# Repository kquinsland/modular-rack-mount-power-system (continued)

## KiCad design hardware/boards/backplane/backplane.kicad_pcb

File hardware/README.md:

# Hardware

Source hardware lives here.

- `boards/`: One KiCad project per physical PCB.
- `libraries/`: Project-local KiCad symbols, footprints, and 3D models shared by all boards.
- `mechanical/`: Enclosure, panel, mounting, and exported mechanical references.

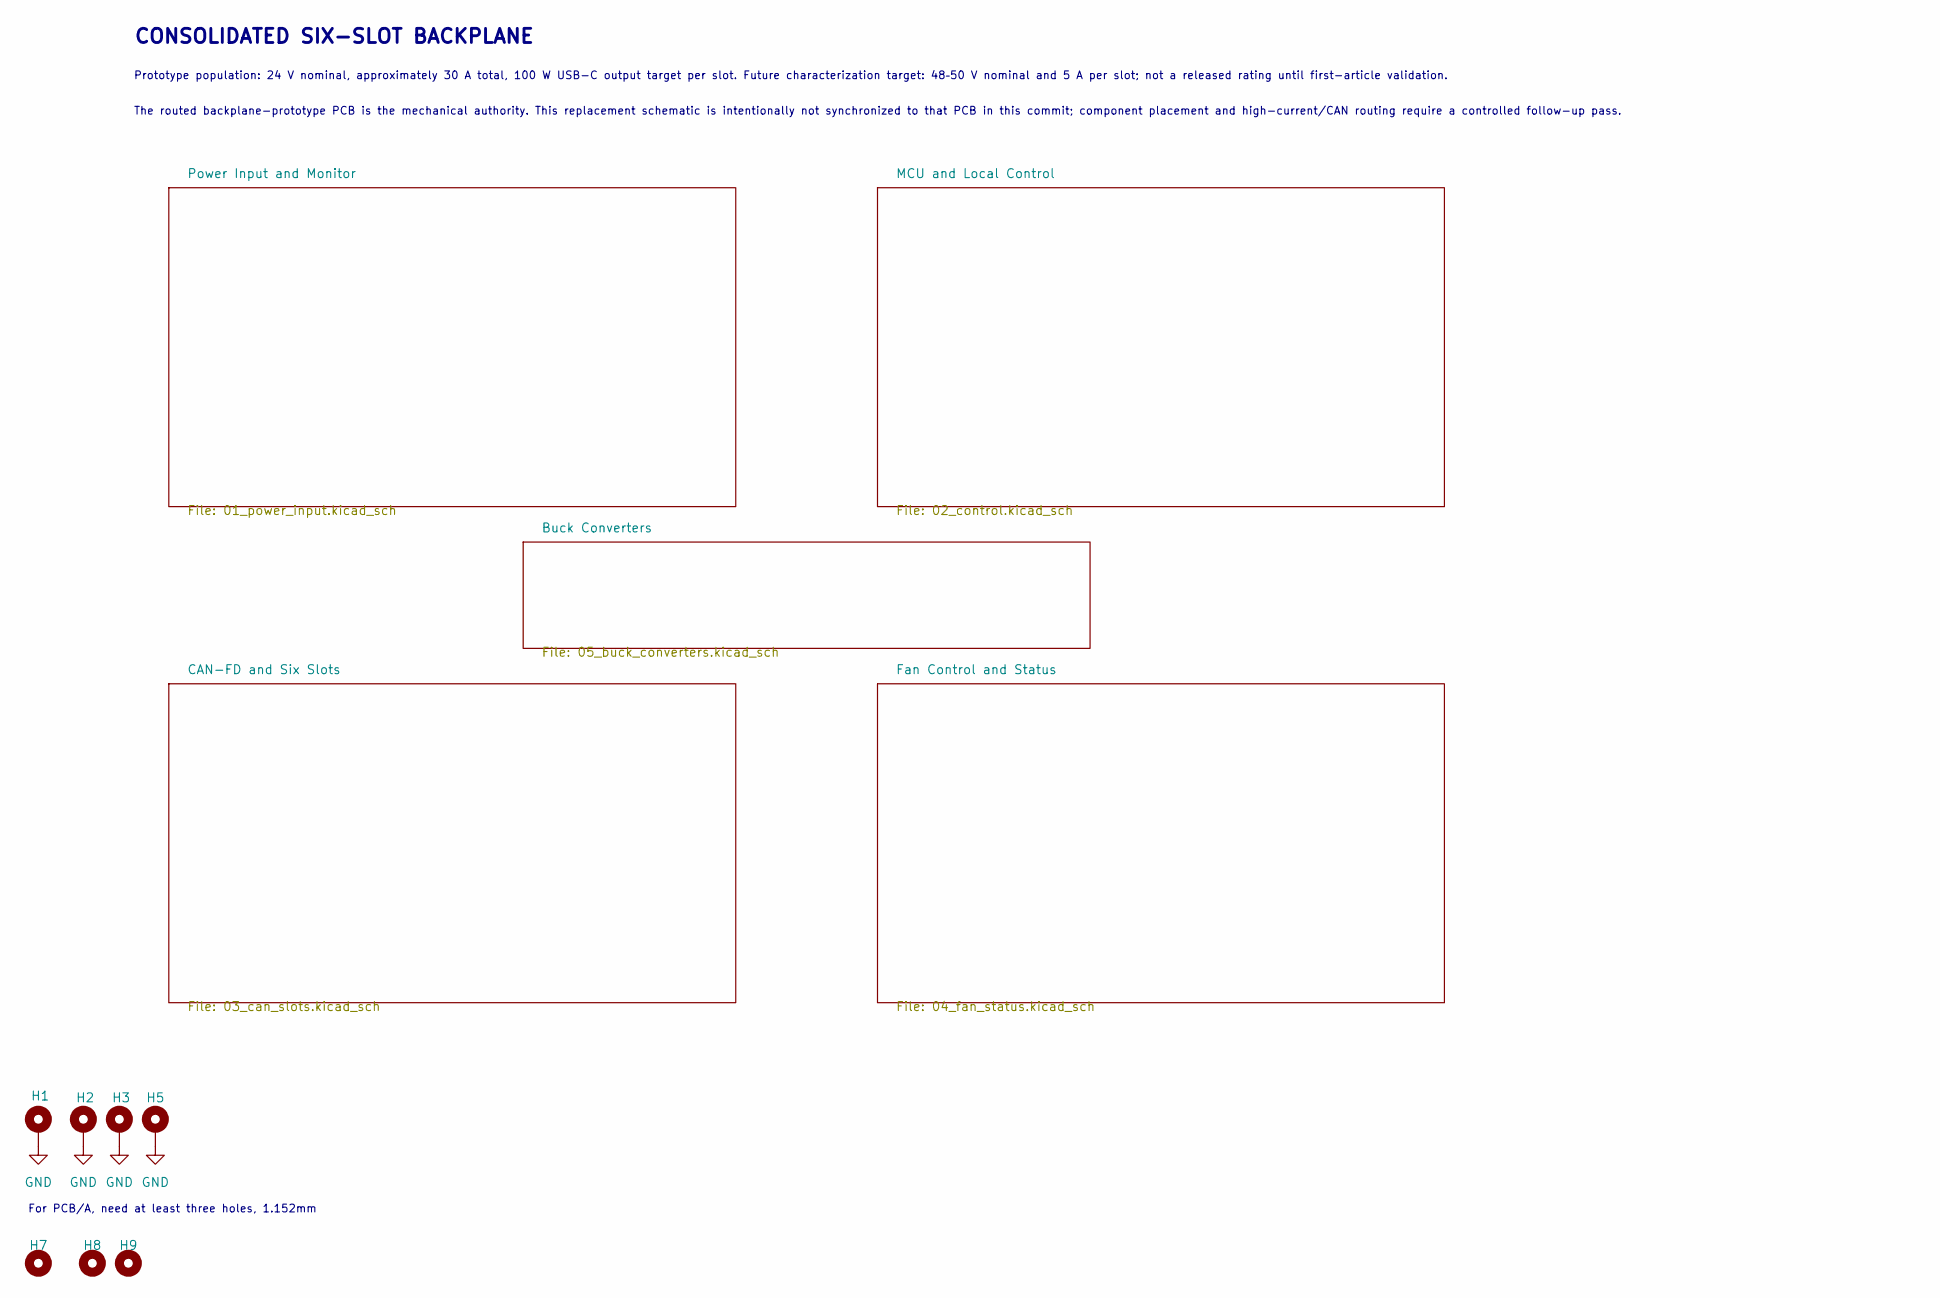
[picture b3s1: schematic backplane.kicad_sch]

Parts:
H1, H2, H3, H5: M2 CHASSIS; MountingHole_2.2mm_M2_Pad_Via_JLC
H7, H8, H9: ToolingHole_1.152mm; MountingHole_JLCPCB_Tooling_1.152mm

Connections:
GND: H1.1 (1_1), H2.1 (1_1), H3.1 (1_1), H5.1 (1_1); also elsewhere on the board

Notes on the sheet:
The routed backplane-prototype PCB is the mechanical authority. This replacement schematic is intentionally not synchronized to that PCB in this commit; component placement and high-current/CAN routing require a controlled follow-up pass.
Prototype population: 24 V nominal, approximately 30 A total, 100 W USB-C output target per slot. Future characterization target: 48–50 V nominal and 5 A per slot; not a released rating until first-article validation.
CONSOLIDATED SIX-SLOT BACKPLANE
For PCB/A, need at least three holes, 1.152mm

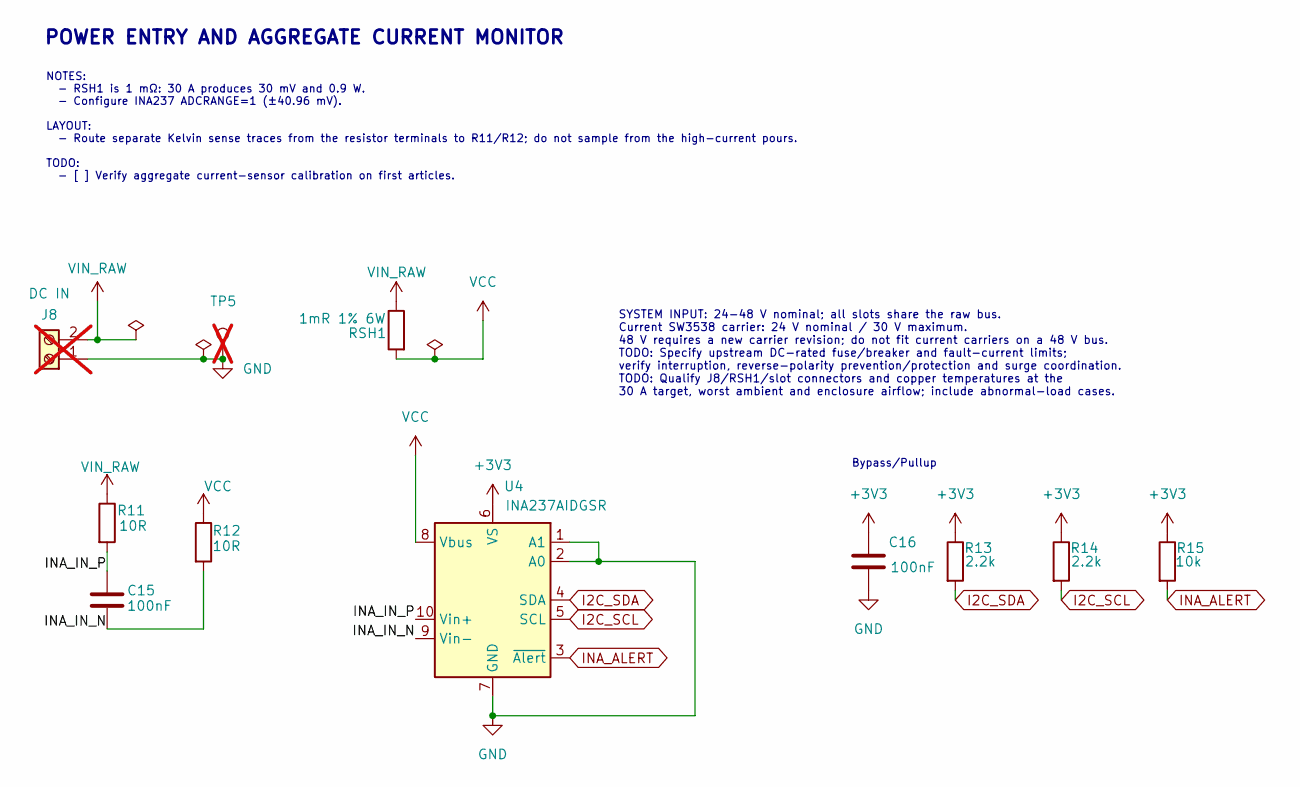
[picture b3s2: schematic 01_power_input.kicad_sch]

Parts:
C15, C16: 100nF; C_0603_1608Metric; Voltage 50 V; MPN CC0603KRX7R9BB104; LCSC C14663
J8: DC IN; DORABO_DB910-6.35-2P-GN-S; MPN DB910-6.35-2P-GN-S; LCSC C395872; not fitted
R11, R12: 10R; R_0603_1608Metric; Tolerance 1%; MPN 0603WAF100JT5E; LCSC C22859
R13, R14: 2.2k; R_0603_1608Metric; Tolerance 1%; MPN 0603WAF2201T5E; LCSC C4190
R15: 10k; R_0603_1608Metric; Tolerance 1%; MPN 0603WAF1002T5E; LCSC C25804
RSH1: 1mR 1% 6W; R_2512_6332Metric; Tolerance 1%; MPN HoLSX2512-6W-1mR-1%; LCSC C19270875
TP5: GND; TestPoint_Pad_D1.5mm; not fitted
U4: INA237AIDGSR; MSOP-10_3x3mm_P0.5mm_0.20mm_Clearance; MPN INA237AIDGSR; LCSC C2864837

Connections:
+3V3: C16.1, R13.1, R14.1, R15.1, U4.6 (VS); also elsewhere on the board
/Power Input and Monitor/INA_IN_N: C15.2, R12.2, U4.9 (Vin-)
/Power Input and Monitor/INA_IN_P: C15.1, R11.2, U4.10 (Vin+)
GND: C16.2, J8.1, TP5.1 (1_1), U4.1 (A1), U4.2 (A0), U4.7 (GND); also elsewhere on the board
I2C_SCL: R14.2, U4.5 (SCL); also elsewhere on the board
I2C_SDA: R13.2, U4.4 (SDA); also elsewhere on the board
INA_ALERT: R15.2, U4.3 (~Alert); also elsewhere on the board
VCC: R12.1, RSH1.2, U4.8 (Vbus); also elsewhere on the board
VIN_RAW: J8.2, R11.1, RSH1.1

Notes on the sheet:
NOTES: - RSH1 is 1 mΩ: 30 A produces 30 mV and 0.9 W. - Configure INA237 ADCRANGE=1 (±40.96 mV). LAYOUT: - Route separate Kelvin sense traces from the resistor terminals to R11/R12; do not sample from the high-current pours. TODO: - [ ] Verify aggregate current-sensor calibration on first articles.
Bypass/Pullup
SYSTEM INPUT: 24-48 V nominal; all slots share the raw bus. Current SW3538 carrier: 24 V nominal / 30 V maximum. 48 V requires a new carrier revision; do not fit current carriers on a 48 V bus. TODO: Specify upstream DC-rated fuse/breaker and fault-current limits; verify interruption, reverse-polar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
POWER ENTRY AND AGGREGATE CURRENT MONITOR

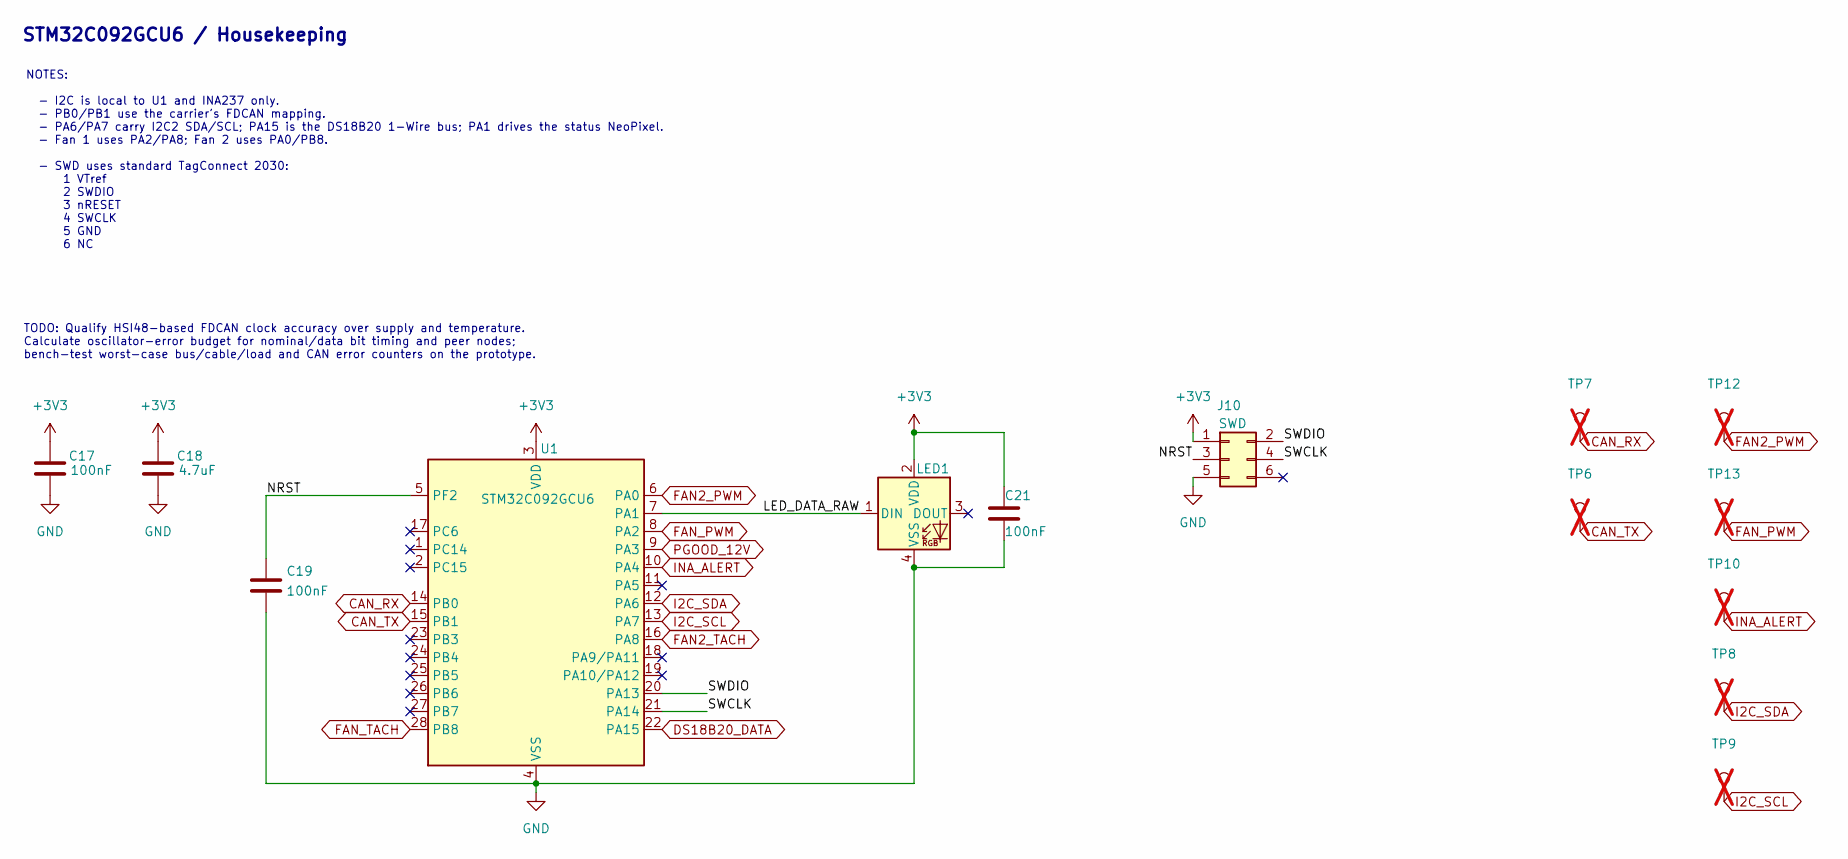
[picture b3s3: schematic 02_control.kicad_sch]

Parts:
C17, C19: 100nF; C_0603_1608Metric; Voltage 50 V; MPN CC0603KRX7R9BB104; LCSC C14663
C18: 4.7uF; C_0603_1608Metric; Voltage 10 V or greater; MPN CL10A475KO8NNNC; LCSC C19666
C21: 100nF; C_0603_1608Metric; MPN CC0603KRX7R9BB104; LCSC C14663
J10: SWD; Tag-Connect_TC2030-IDC-NL_2x03_P1.27mm_Vertical; MPN TC2030-IDC-NL
LED1: WS2812B-4020-V6; LED_Worldsemi_WS2812B-4020-V6_SideView; MPN WS2812B-4020-V6; LCSC C52941387
TP6: CAN_TX; TestPoint_Pad_D1.5mm; not fitted
TP7: CAN_RX; TestPoint_Pad_D1.5mm; not fitted
TP8: I2C_SDA; TestPoint_Pad_D1.5mm; not fitted
TP9: I2C_SCL; TestPoint_Pad_D1.5mm; not fitted
TP10: INA_ALERT; TestPoint_Pad_D1.5mm; not fitted
TP12, TP13: FAN_PWM; TestPoint_Pad_D1.5mm; not fitted
U1: STM32C092GCU6; QFN-28_4x4mm_P0.5mm; MPN STM32C092GCU6; LCSC C44847705

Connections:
+3V3: C17.1, C18.1, C21.1, J10.1, LED1.2 (VDD), U1.3 (VDD); also elsewhere on the board
/MCU and Local Control/LED_DATA_RAW: LED1.1 (DIN), U1.7 (PA1)
/MCU and Local Control/NRST: C19.1, J10.3, U1.5 (PF2)
/MCU and Local Control/SWCLK: J10.4, U1.21 (PA14)
/MCU and Local Control/SWDIO: J10.2, U1.20 (PA13)
CAN_RX: TP7.1 (1_1), U1.14 (PB0); also elsewhere on the board
CAN_TX: TP6.1 (1_1), U1.15 (PB1); also elsewhere on the board
DS18B20_DATA: U1.22 (PA15); also elsewhere on the board
FAN2_PWM: TP12.1 (1_1), U1.6 (PA0); also elsewhere on the board
FAN2_TACH: U1.16 (PA8); also elsewhere on the board
FAN_PWM: TP13.1 (1_1), U1.8 (PA2); also elsewhere on the board
FAN_TACH: U1.28 (PB8); also elsewhere on the board
GND: C17.2, C18.2, C19.2, C21.2, J10.5, LED1.4 (VSS), U1.4 (VSS); also elsewhere on the board
I2C_SCL: TP9.1 (1_1), U1.13 (PA7); also elsewhere on the board
I2C_SDA: TP8.1 (1_1), U1.12 (PA6); also elsewhere on the board
INA_ALERT: TP10.1 (1_1), U1.10 (PA4); also elsewhere on the board
PGOOD_12V: U1.9 (PA3); also elsewhere on the board

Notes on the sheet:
TODO: Qualify HSI48-based FDCAN clock accuracy over supply and temperature. Calculate oscillator-error budget for nominal/data bit timing and peer nodes; bench-test worst-case bus/cable/load and CAN error counters on the prototype.
STM32C092GCU6 / Housekeeping
NOTES: - I2C is local to U1 and INA237 only. - PB0/PB1 use the carrier's FDCAN mapping. - PA6/PA7 carry I2C2 SDA/SCL; PA15 is the DS18B20 1-Wire bus; PA1 drives the status NeoPixel. - Fan 1 uses PA2/PA8; Fan 2 uses PA0/PB8. - SWD uses standard TagConnect 2030: 1 VTref 2 SWDIO 3 nRESET 4 SWCLK 5 GND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

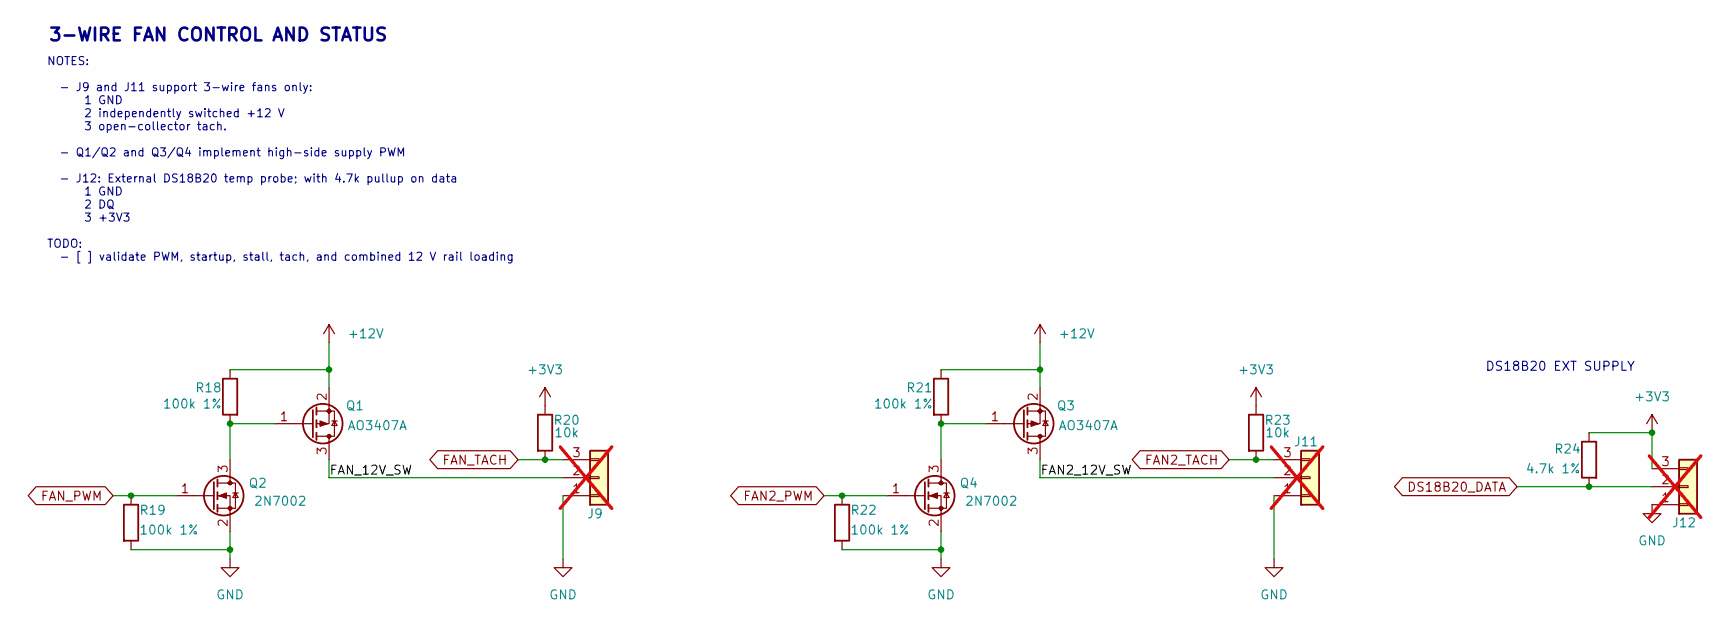
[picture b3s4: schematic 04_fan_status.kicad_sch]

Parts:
J9, J11: 12V 3-WIRE FAN; FanPinHeader_1x03_P2.54mm_Vertical_JLC_Edge; MPN TBD / user fan header; not fitted
J12: DS18B20 EXT SUPPLY; PinHeader_1x03_P2.54mm_Vertical; MPN TBD / user pin header; not fitted
Q1, Q3: AO3407A; SOT-23; MPN AO3407A; LCSC C15155
Q2, Q4: 2N7002; SOT-23; MPN 2N7002; LCSC C8545
R18, R19, R21, R22: 100k 1%; R_0603_1608Metric; Tolerance 1%; MPN 0603WAF1003T5E; LCSC C25803
R20, R23: 10k; R_0603_1608Metric; Tolerance 1%; MPN 0603WAF1002T5E; LCSC C25804
R24: 4.7k 1%; R_0603_1608Metric; Tolerance 1%; MPN 0603WAF4701T5E; LCSC C23162

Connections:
+3V3: J12.3, R20.1, R23.1, R24.1; also elsewhere on the board
+12V: Q1.2 (S), Q3.2 (S), R18.1, R21.1; also elsewhere on the board
/Fan Control and Status/FAN2_12V_SW: J11.2, Q3.3 (D)
/Fan Control and Status/FAN_12V_SW: J9.2, Q1.3 (D)
DS18B20_DATA: J12.2, R24.2; also elsewhere on the board
FAN2_PWM: Q4.1 (G), R22.1; also elsewhere on the board
FAN2_TACH: J11.3, R23.2; also elsewhere on the board
FAN_PWM: Q2.1 (G), R19.1; also elsewhere on the board
FAN_TACH: J9.3, R20.2; also elsewhere on the board
GND: J9.1, J11.1, J12.1, Q2.2 (S), Q4.2 (S), R19.2, R22.2; also elsewhere on the board
unnamed: Q1.1 (G), Q2.3 (D), R18.2
unnamed: Q3.1 (G), Q4.3 (D), R21.2

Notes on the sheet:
NOTES: - J9 and J11 support 3-wire fans only: 1 GND 2 independently switched +12 V 3 open-collector tach. - Q1/Q2 and Q3/Q4 implement high-side supply PWM - J12: External DS18B20 temp probe; with 4.7k pullup on data 1 GND 2 DQ 3 +3V3 TODO: - [ ] validate PWM, startup, stall, tach, and combined 12 V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
3-WIRE FAN CONTROL AND STATUS
DS18B20 EXT SUPPLY

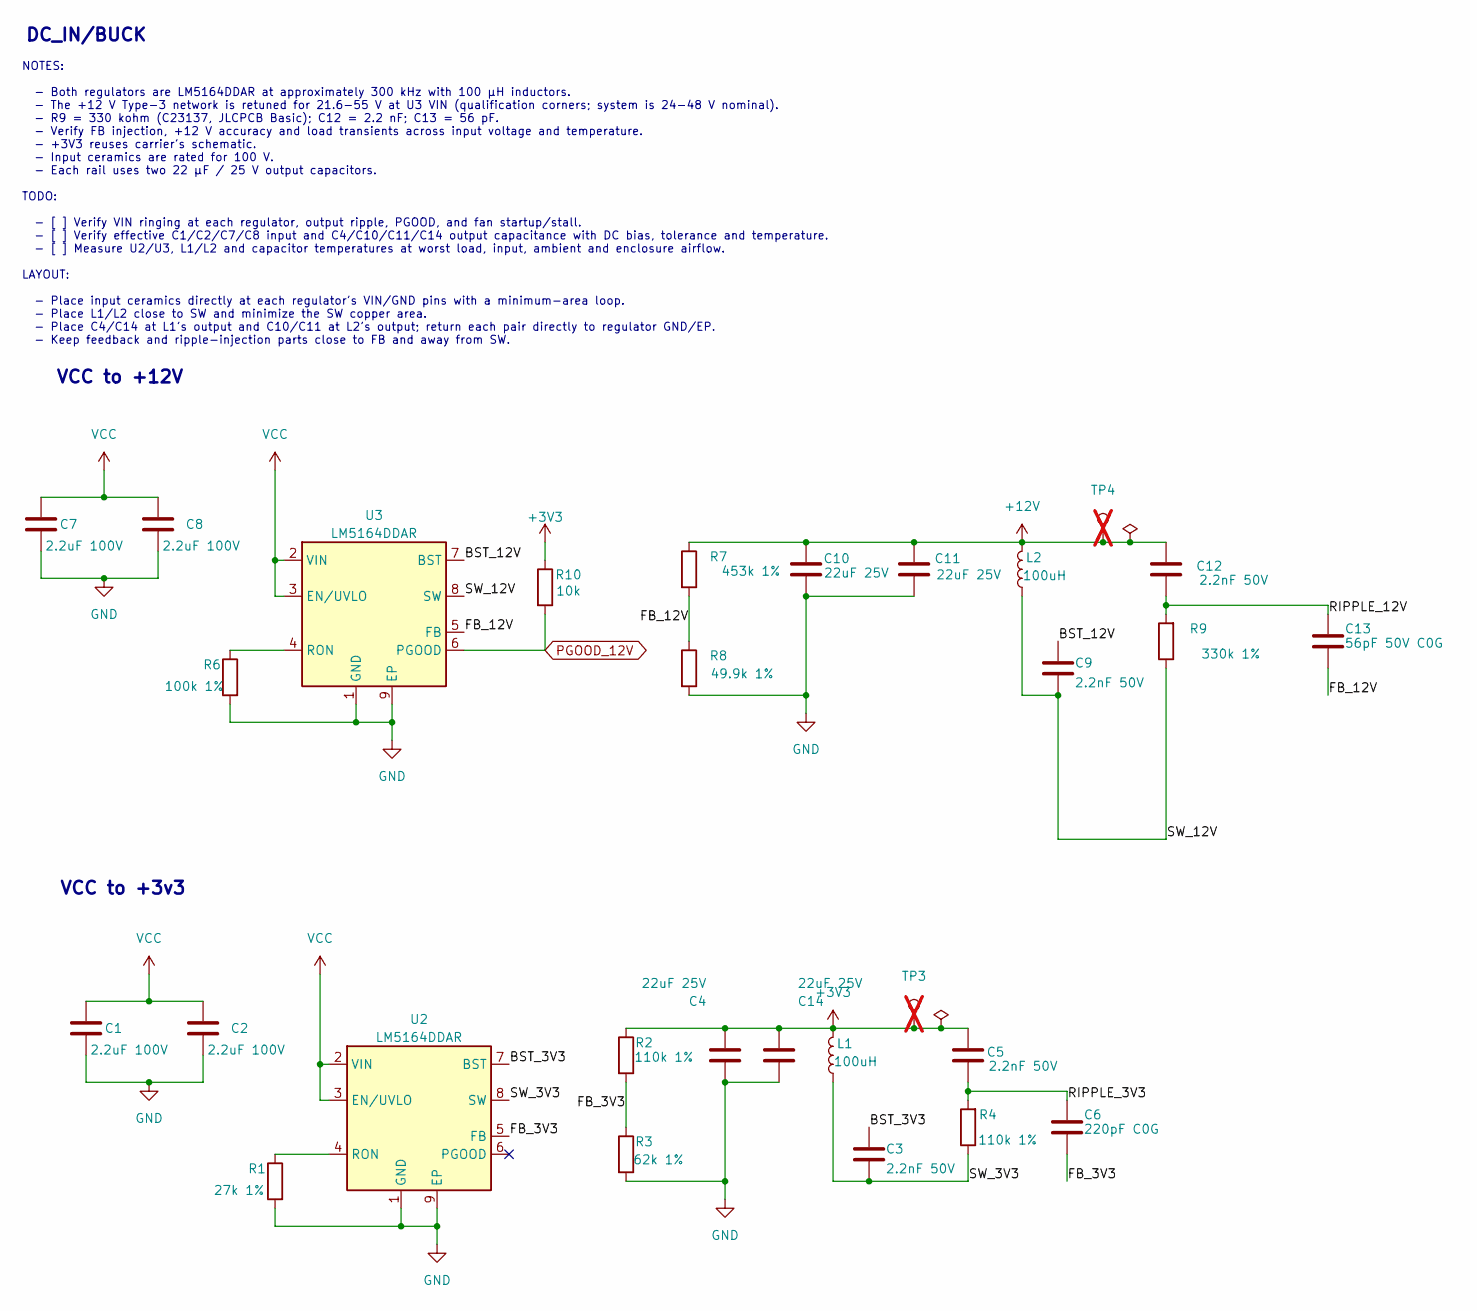
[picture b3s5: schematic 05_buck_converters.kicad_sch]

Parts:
C1, C2, C7, C8: 2.2uF 100V; C_1210_3225Metric; Voltage 100 V; MPN CL32B225KCJSNNE; LCSC C55151
C3, C5, C9, C12: 2.2nF 50V; C_0603_1608Metric; Voltage 50 V; MPN 0603B222K500NT; LCSC C1604
C4, C10, C11, C14: 22uF 25V; C_0805_2012Metric; Voltage 25 V; MPN CL21A226MAQNNNE; LCSC C45783
C6: 220pF C0G; C_0603_1608Metric; Voltage 50 V; MPN CC0603JRNPO9BN221; LCSC C106210
C13: 56pF 50V C0G; C_0603_1608Metric; Voltage 50 V; MPN 0603CG560J500NT; LCSC C1676
L1, L2: 100uH; L_PRODTech_PSPMAA0805; MPN PSPMAA0805-101M-ANP; LCSC C2962892
R1: 27k 1%; R_0603_1608Metric; Tolerance 1%; MPN 0603WAF2702T5E; LCSC C22967
R2, R4: 110k 1%; R_0603_1608Metric; Tolerance 1%; MPN 0603WAF1103T5E; LCSC C25805
R3: 62k 1%; R_0603_1608Metric; Tolerance 1%; MPN 0603WAF6202T5E; LCSC C23221
R6: 100k 1%; R_0603_1608Metric; Tolerance 1%; MPN 0603WAF1003T5E; LCSC C25803
R7: 453k 1%; R_0603_1608Metric; Tolerance 1%; MPN 0603WAF4533T5E; LCSC C25818
R8: 49.9k 1%; R_0603_1608Metric; Tolerance 1%; MPN 0603WAF4992T5E; LCSC C23184
R9: 330k 1%; R_0603_1608Metric; Tolerance 1%; MPN 0603WAF3303T5E; LCSC C23137
R10: 10k; R_0603_1608Metric; Tolerance 1%; MPN 0603WAF1002T5E; LCSC C25804
TP3: +3V3; TestPoint_Pad_D1.5mm; not fitted
TP4: +12V; TestPoint_Pad_D1.5mm; not fitted
U2, U3: LM5164DDAR; TI_SO-PowerPAD-8; MPN LM5164DDAR; LCSC C477928

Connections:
+3V3: C4.1, C5.2, C14.1, L1.2, R2.1, R10.1, TP3.1 (1_1); also elsewhere on the board
+12V: C10.1, C11.1, C12.2, L2.2, R7.1, TP4.1 (1_1); also elsewhere on the board
/Buck Converters/BST_3V3: C3.1, U2.7 (BST)
/Buck Converters/BST_12V: C9.1, U3.7 (BST)
/Buck Converters/FB_3V3: C6.2, R2.2, R3.1, U2.5 (FB)
/Buck Converters/FB_12V: C13.2, R7.2, R8.1, U3.5 (FB)
/Buck Converters/RIPPLE_3V3: C5.1, C6.1, R4.2
/Buck Converters/RIPPLE_12V: C12.1, C13.1, R9.2
/Buck Converters/SW_3V3: C3.2, L1.1, R4.1, U2.8 (SW)
/Buck Converters/SW_12V: C9.2, L2.1, R9.1, U3.8 (SW)
GND: C1.2, C2.2, C4.2, C7.2, C8.2, C10.2, C11.2, C14.2, R1.2, R3.2, R6.2, R8.2, U2.1 (GND), U2.9 (EP), U3.1 (GND), U3.9 (EP); also elsewhere on the board
unnamed: R1.1, U2.4 (RON)
unnamed: R6.1, U3.4 (RON)
PGOOD_12V: R10.2, U3.6 (PGOOD); also elsewhere on the board
VCC: C1.1, C2.1, C7.1, C8.1, U2.2 (VIN), U2.3 (EN/UVLO), U3.2 (VIN), U3.3 (EN/UVLO); also elsewhere on the board

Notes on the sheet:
DC_IN/BUCK
NOTES: - Both regulators are LM5164DDAR at approximately 300 kHz with 100 µH inductors. - The +12 V Type-3 network is retuned for 21.6-55 V at U3 VIN (qualification corners; system is 24-48 V nominal). - R9 = 330 kohm (C23137, JLCPCB Basic); C12 = 2.2 nF; C13 = 56 pF. - Verify FB injection, +12 V a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
VCC to +3v3
VCC to +12V

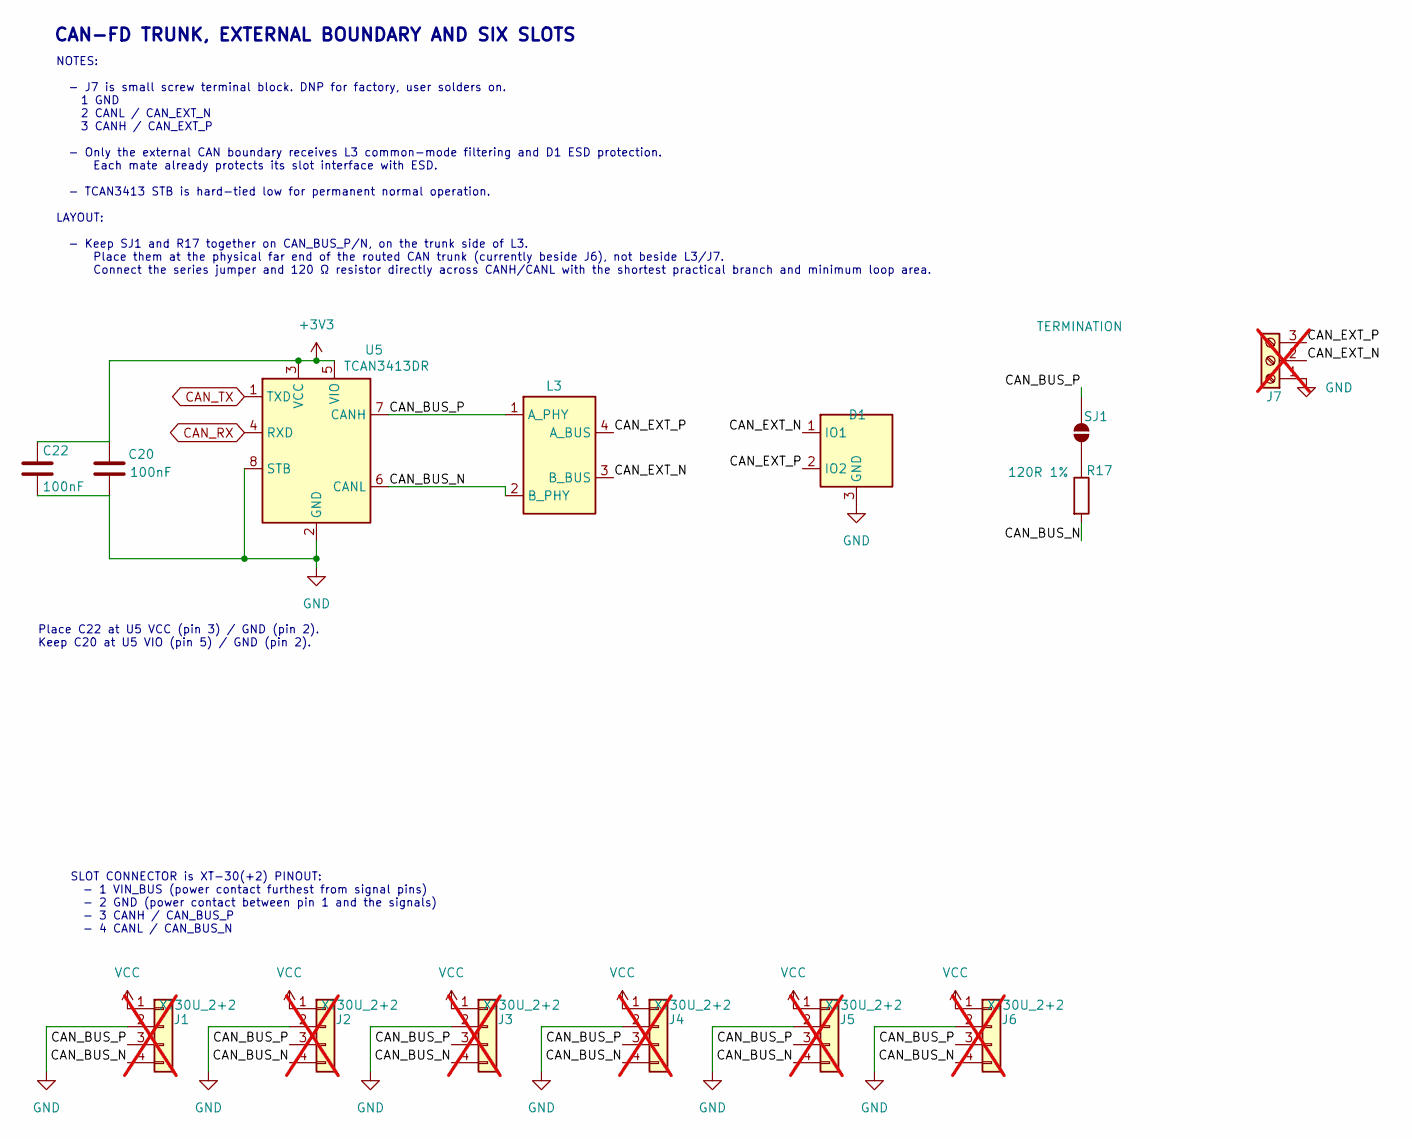
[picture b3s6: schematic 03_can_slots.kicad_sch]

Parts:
C20, C22: 100nF; C_0603_1608Metric; Voltage 50 V; MPN CC0603KRX7R9BB104; LCSC C14663
D1: PESD2CANFD27V-TR; SOT-23; MPN PESD2CANFD27V-TR; LCSC C552488
J1, J2, J3, J4, J5, J6: XT30U_2+2; Amass_XT30U_2plus2_F; MPN XT30U(2+2)-F.G.B; LCSC C30170181; not fitted
J7: XY308-2.54-3P / EXTERNAL CAN; TerminalBlock_Xinya_XY308-2.54-3P_1x03_P2.54mm_Horizontal; MPN XY308-2.54-3P; LCSC C557686; not fitted
L3: ACT1210D-101-2P-TL00; L_CommonModeChoke_TDK_ACT1210D; MPN ACT1210D-101-2P-TL00; LCSC C3039743
R17: 120R 1%; R_0603_1608Metric; Tolerance 1%; MPN 0603WAF1200T5E; LCSC C22787
SJ1: TERMINATION; SolderJumper-2_P1.3mm_Open_Pad1.0x1.5mm; MPN PCB solder jumper
U5: TCAN3413DR; SOIC-8_3.9x4.9mm_P1.27mm; MPN TCAN3413DR; LCSC C22433320

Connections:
+3V3: C20.1, C22.1, U5.3 (VCC), U5.5 (VIO); also elsewhere on the board
/CAN-FD and Six Slots/CAN_BUS_N: J1.4, J2.4, J3.4, J4.4, J5.4, J6.4, L3.2 (B_PHY), R17.2, U5.6 (CANL)
/CAN-FD and Six Slots/CAN_BUS_P: J1.3, J2.3, J3.3, J4.3, J5.3, J6.3, L3.1 (A_PHY), SJ1.1 (A), U5.7 (CANH)
/CAN-FD and Six Slots/CAN_EXT_N: D1.1 (IO1), J7.2, L3.3 (B_BUS)
/CAN-FD and Six Slots/CAN_EXT_P: D1.2 (IO2), J7.3, L3.4 (A_BUS)
CAN_RX: U5.4 (RXD); also elsewhere on the board
CAN_TX: U5.1 (TXD); also elsewhere on the board
GND: C20.2, C22.2, D1.3 (GND), J1.2, J2.2, J3.2, J4.2, J5.2, J6.2, J7.1, U5.2 (GND), U5.8 (STB); also elsewhere on the board
unnamed: R17.1, SJ1.2 (B)
VCC: J1.1, J2.1, J3.1, J4.1, J5.1, J6.1; also elsewhere on the board

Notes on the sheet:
SLOT CONNECTOR is XT-30(+2) PINOUT: - 1 VIN_BUS (power contact furthest from signal pins) - 2 GND (power contact between pin 1 and the signals) - 3 CANH / CAN_BUS_P - 4 CANL / CAN_BUS_N
NOTES: - J7 is small screw terminal block. DNP for factory, user solders on. 1 GND 2 CANL / CAN_EXT_N 3 CANH / CAN_EXT_P - Only the external CAN boundary receives L3 common-mode filtering and D1 ESD protection. Each mate already protects its slot interface with ESD. - TCAN3413 STB is hard-tied low 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
CAN-FD TRUNK, EXTERNAL BOUNDARY AND SIX SLOTS
Place C22 at U5 VCC (pin 3) / GND (pin 2). Keep C20 at U5 VIO (pin 5) / GND (pin 2).

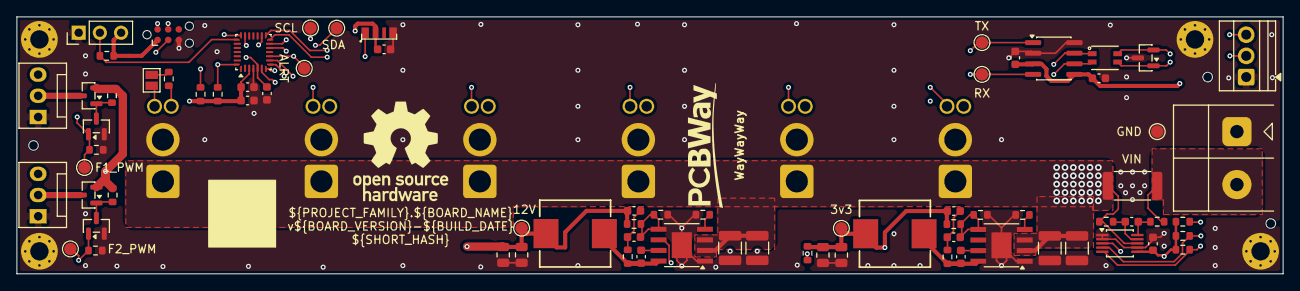
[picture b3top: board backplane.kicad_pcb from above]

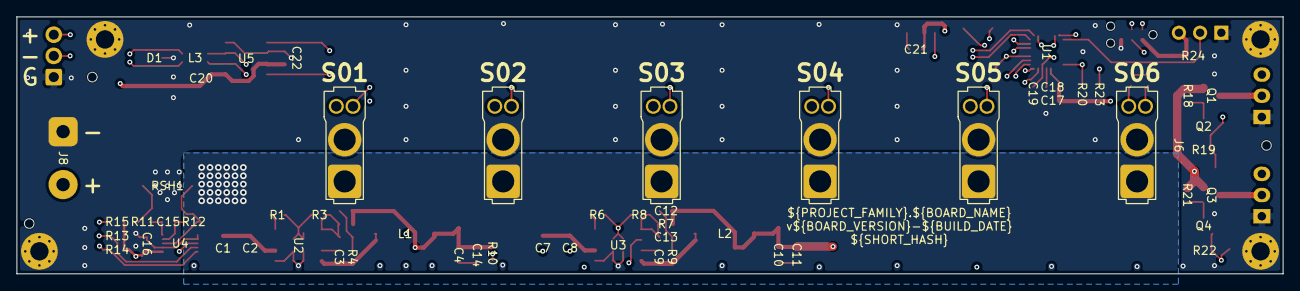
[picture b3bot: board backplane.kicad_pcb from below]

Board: 4 copper layers, 151.8 x 30.8 mm, 90 parts (10 on the bottom side), 41 nets.

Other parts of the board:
LOGO_PCBWAY: PCBWay_Logo_15mm

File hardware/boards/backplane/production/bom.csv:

Designator,Footprint,Quantity,Value,LCSC Part #
"C1, C2, C7, C8",C_1210_3225Metric,4,2.2uF 100V,C55151
"C3, C5, C9, C12",C_0603_1608Metric,4,2.2nF 50V,C1604
"C4, C10, C11, C14",C_0805_2012Metric,4,22uF 25V,C45783
C6,C_0603_1608Metric,1,220pF C0G,C106210
C13,C_0603_1608Metric,1,56pF 50V C0G,C1676
"C15, C16, C17, C19, C20, C21, C22",C_0603_1608Metric,7,100nF,C14663
C18,C_0603_1608Metric,1,4.7uF,C19666
D1,SOT-23,1,PESD2CANFD27V-TR,C552488
"L1, L2",L_PRODTech_PSPMAA0805,2,100uH,C2962892
L3,L_CommonModeChoke_TDK_ACT1210D,1,ACT1210D-101-2P-TL00,C3039743
LED1,LED_Worldsemi_WS2812B-4020-V6_SideView,1,WS2812B-4020-V6,C52941387
"Q1, Q3",SOT-23,2,AO3407A,C15155
"Q2, Q4",SOT-23,2,2N7002,C8545
R1,R_0603_1608Metric,1,27k 1%,C22967
"R2, R4",R_0603_1608Metric,2,110k 1%,C25805
R3,R_0603_1608Metric,1,62k 1%,C23221
"R6, R18, R19, R21, R22",R_0603_1608Metric,5,100k 1%,C25803
R7,R_0603_1608Metric,1,453k 1%,C25818
R8,R_0603_1608Metric,1,49.9k 1%,C23184
R9,R_0603_1608Metric,1,330k 1%,C23137
"R10, R15, R20, R23",R_0603_1608Metric,4,10k,C25804
"R11, R12",R_0603_1608Metric,2,10R,C22859
"R13, R14",R_0603_1608Metric,2,2.2k,C4190
R17,R_0603_1608Metric,1,120R 1%,C22787
R24,R_0603_1608Metric,1,4.7k 1%,C23162
RSH1,R_2512_6332Metric,1,1mR 1% 6W,C19270875
U1,QFN-28_4x4mm_P0.5mm,1,STM32C092GCU6,C44847705
"U2, U3",TI_SO-PowerPAD-8,2,LM5164DDAR,C477928
U4,MSOP-10_3x3mm_P0.5mm_0.20mm_Clearance,1,INA237AIDGSR,C2864837
U5,SOIC-8_3.9x4.9mm_P1.27mm,1,TCAN3413DR,C22433320

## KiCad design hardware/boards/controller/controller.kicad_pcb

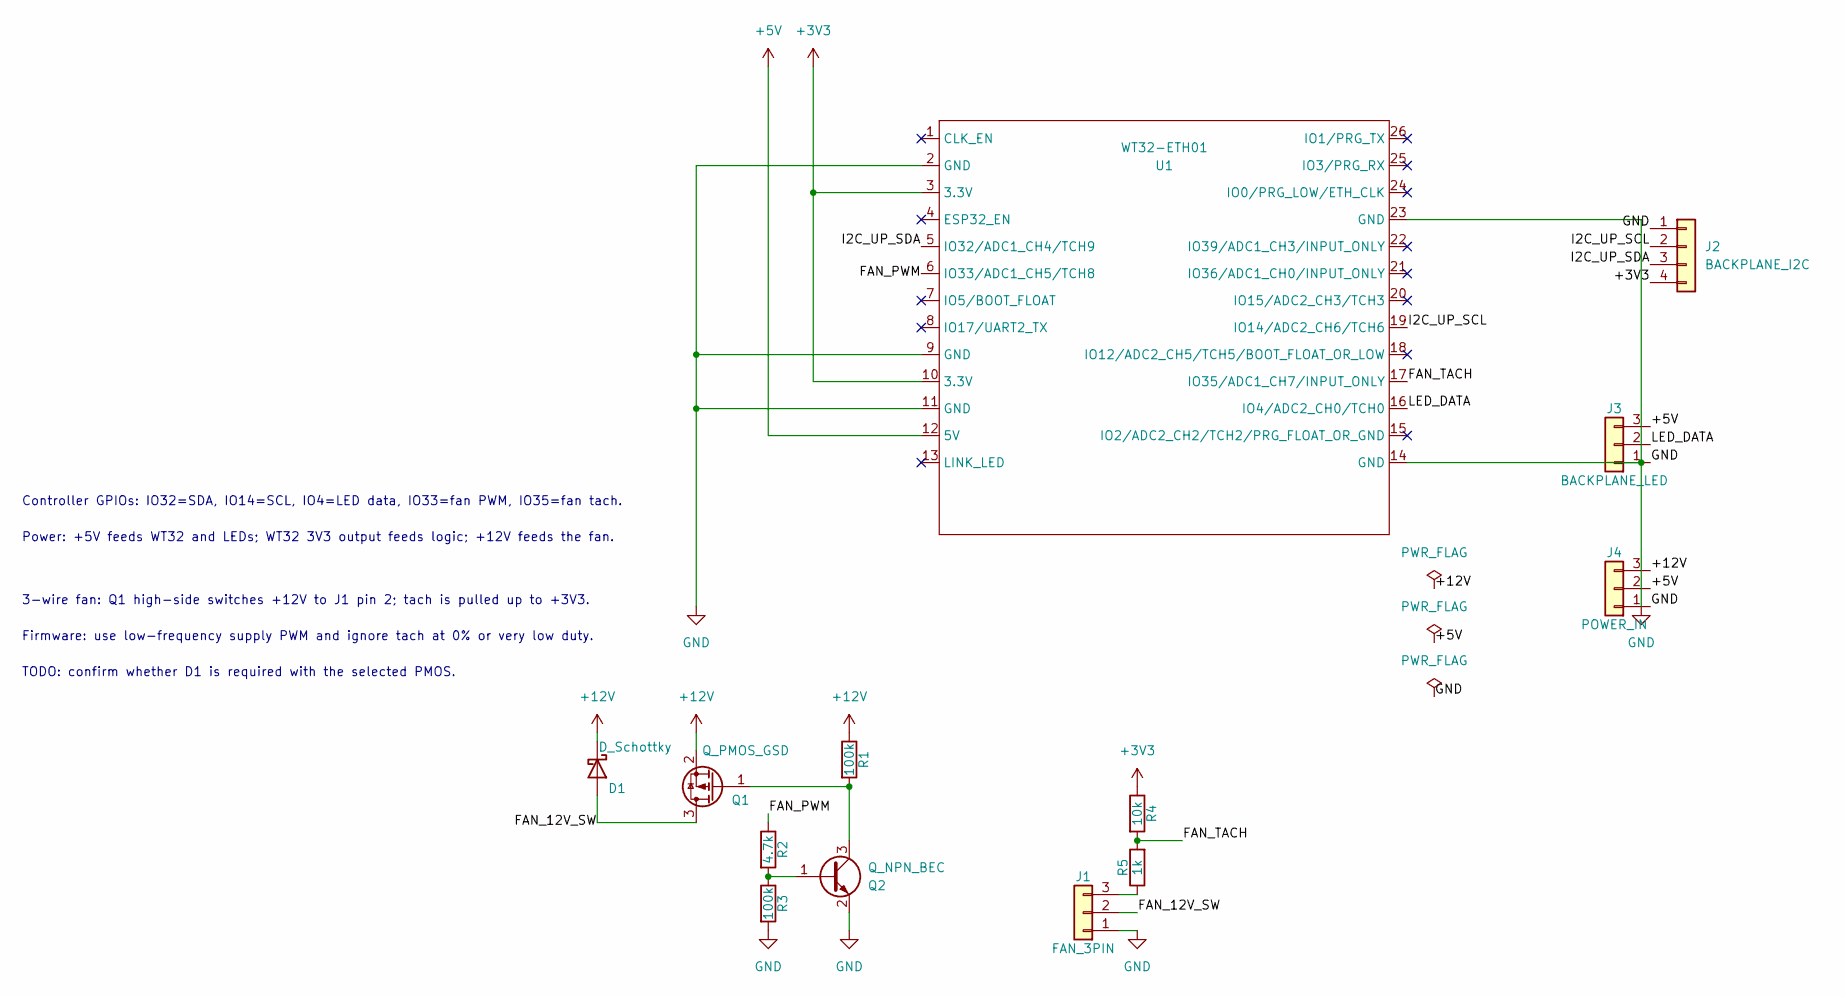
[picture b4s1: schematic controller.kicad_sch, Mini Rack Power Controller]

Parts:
D1: D_Schottky; D_SOD-123; Part_source LCSC,XXXXXXX
J1: FAN_3PIN; PinHeader_1x03_P2.54mm_Vertical; Part_source LCSC,XXXXXXX
J2: BACKPLANE_I2C; PinHeader_1x04_P2.54mm_Vertical
J3: BACKPLANE_LED; PinHeader_1x03_P2.54mm_Vertical; Part_source LCSC,XXXXXXX
J4: POWER_IN; PinHeader_1x03_P2.54mm_Vertical; Part_source LCSC,XXXXXXX
Q1: Q_PMOS_GSD; SOT-23; Part_source LCSC,XXXXXXX
Q2: Q_NPN_BEC; SOT-23; Part_source LCSC,XXXXXXX
R1, R3: 100k; R_0603_1608Metric; Part_source LCSC,XXXXXXX
R2: 4.7k; R_0603_1608Metric; Part_source LCSC,XXXXXXX
R4: 10k; R_0603_1608Metric; Part_source LCSC,XXXXXXX
R5: 1k; R_0603_1608Metric; Part_source LCSC,XXXXXXX
U1: WT32-ETH01; Part_source LCSC,XXXXXXX

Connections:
+3V3: J2.4, R4.1, U1.3 (3.3V), U1.10 (3.3V)
+5V: J3.3, J4.2, U1.12 (5V)
+12V: D1.1 (K), J4.3, Q1.2 (S), R1.1
/FAN_12V_SW: D1.2 (A), J1.2, Q1.3 (D)
/FAN_PWM: R2.1, U1.6 (IO33/ADC1_CH5/TCH8)
/FAN_TACH: R4.2, R5.2, U1.17 (IO35/ADC1_CH7/INPUT_ONLY)
/I2C_UP_SCL: J2.2, U1.19 (IO14/ADC2_CH6/TCH6)
/I2C_UP_SDA: J2.3, U1.5 (IO32/ADC1_CH4/TCH9)
/LED_DATA: J3.2, U1.16 (IO4/ADC2_CH0/TCH0)
GND: J1.1, J2.1, J3.1, J4.1, Q2.2 (E), R3.2, U1.2 (GND), U1.9 (GND), U1.11 (GND), U1.14 (GND), U1.23 (GND)
unnamed: J1.3, R5.1
unnamed: Q1.1 (G), Q2.3 (C), R1.2
unnamed: Q2.1 (B), R2.2, R3.1

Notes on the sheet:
Controller GPIOs: IO32=SDA, IO14=SCL, IO4=LED data, IO33=fan PWM, IO35=fan tach.
Power: +5V feeds WT32 and LEDs; WT32 3V3 output feeds logic; +12V feeds the fan.
3-wire fan: Q1 high-side switches +12V to J1 pin 2; tach is pulled up to +3V3.
Firmware: use low-frequency supply PWM and ignore tach at 0% or very low duty.
TODO: confirm whether D1 is required with the selected PMOS.

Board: 2 copper layers, 13 parts (0 on the bottom side), 13 nets, no tracks yet.

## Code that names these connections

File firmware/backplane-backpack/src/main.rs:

#![no_main]
#![no_std]

mod channels;
mod tasks;

use backplane_backpack_firmware::board::{
    CAN_DATA_BITRATE, CAN_NOMINAL_BITRATE, MUX_RESET_AVAILABLE,
};
use backplane_backpack_firmware::config_store::ConfigStore;
use backplane_backpack_firmware::config_store::stm32::Stm32ConfigFlash;
use backplane_backpack_firmware::fan::{FanDrive, THREE_WIRE_FREQUENCY_HZ_PROVISIONAL};
use backplane_backpack_firmware::status::STATUS_WORDS;
use backplane_backpack_firmware::supervisor::IWDG_TIMEOUT_US_PROVISIONAL;
use embassy_executor::Spawner;
use embassy_stm32::bind_interrupts;
use embassy_stm32::can::config::{GlobalFilter, NonMatchingFilter};
use embassy_stm32::can::{self, CanConfigurator};
use embassy_stm32::dma;
use embassy_stm32::gpio::{Level, Output, OutputType, Pull, Speed};
use embassy_stm32::i2c::{self, I2c};
use embassy_stm32::peripherals;
use embassy_stm32::rcc::{Hsi, HsiKerDiv, HsiSysDiv};
use embassy_stm32::time::Hertz;
use embassy_stm32::timer;
use embassy_stm32::timer::input_capture::{CapturePin, InputCapture};
use embassy_stm32::timer::low_level::CountingMode;
use embassy_stm32::timer::simple_pwm::{PwmPin, SimplePwm};
use embassy_stm32::wdg::IndependentWatchdog;
use embassy_time::{Duration, Timer};
use panic_halt as _;
use pdcan_protocol::ResetFlags;
use pdcan_types::{NodeUid, PersistentSettings};
use static_cell::StaticCell;

const I2C_FREQUENCY_HZ: u32 = 100_000;
const I2C_TIMEOUT_MS_PROVISIONAL: u64 = 100;
const TACH_TIMER_HZ_PROVISIONAL: u32 = 1_000_000;
const WS2812_TIMER_HZ: u32 = 800_000;
const STATUS_DMA_CAPACITY: usize = STATUS_WORDS + 8;

static STATUS_DMA_BUFFER: StaticCell<[u16; STATUS_DMA_CAPACITY]> = StaticCell::new();

bind_interrupts!(struct Irqs {
    FDCAN1_IT0 => can::IT0InterruptHandler<peripherals::FDCAN1>;
    FDCAN1_IT1 => can::IT1InterruptHandler<peripherals::FDCAN1>;
    I2C2 => i2c::EventInterruptHandler<peripherals::I2C2>, i2c::ErrorInterruptHandler<peripherals::I2C2>;
    DMA1_CHANNEL1 => dma::InterruptHandler<peripherals::DMA1_CH1>;
    DMA1_CHANNEL2_3 => dma::InterruptHandler<peripherals::DMA1_CH2>, dma::InterruptHandler<peripherals::DMA1_CH3>;
    TIM17 => timer::CaptureCompareInterruptHandler<peripherals::TIM17>;
});

#[embassy_executor::main]
async fn main(spawner: Spawner) -> ! {
    let mut config = embassy_stm32::Config::default();
    config.rcc.hsi = Some(Hsi {
        sys_div: HsiSysDiv::DIV1,
        ker_div: HsiKerDiv::DIV1,
    });
    let p = embassy_stm32::init(config);
    let reset_flags = capture_reset_flags();

    // Rev B presents only upstream I2C, 3.3 V, and ground at the backplane
    // boundary. Its backplane-local TCA9548A reset is not MCU-controlled, and
    // the PCA9554 gate pull-downs hold every slot off at cold power-on.
    let mux_reset = if MUX_RESET_AVAILABLE {
        let mut reset = Output::new(p.PA3, Level::Low, Speed::Low);
        Timer::after_millis(1).await;
        reset.set_high();
        Some(reset)
    } else {
        None
    };
    let can_standby = Output::new(p.PA4, Level::High, Speed::Low);

    let mut fan_pwm = SimplePwm::new(
        p.TIM2,
        Some(PwmPin::new(p.PA0, OutputType::PushPull)),
        None,
        None,
        None,
        Hertz::hz(THREE_WIRE_FREQUENCY_HZ_PROVISIONAL),
        CountingMode::EdgeAlignedUp,
    );
    {
        let mut channel = fan_pwm.ch1();
        channel.set_duty_cycle_percent(FanDrive::BOOT_SAFE.pa0_high_percent);
        channel.enable();
    }
    let fan_tach = InputCapture::new(
        p.TIM17,
        Some(CapturePin::new(p.PA1, Pull::None)),
        None,
        None,
        None,
        Irqs,
        Hertz::hz(TACH_TIMER_HZ_PROVISIONAL),
        CountingMode::EdgeAlignedUp,
    );

    let status_pwm = SimplePwm::new(
        p.TIM15,
        Some(PwmPin::new(p.PA2, OutputType::PushPull)),
        None,
        None,
        None,
        Hertz::hz(WS2812_TIMER_HZ),
        CountingMode::EdgeAlignedUp,
    );
    let status_buffer = STATUS_DMA_BUFFER.init([0; STATUS_DMA_CAPACITY]);
    let status_output =
        status_pwm
            .split()
            .ch1
            .into_ring_buffered_channel(p.DMA1_CH3, status_buffer, Irqs);

    let mut i2c_config = i2c::Config::default();
    i2c_config.frequency = Hertz::hz(I2C_FREQUENCY_HZ);
    i2c_config.timeout = Duration::from_millis(I2C_TIMEOUT_MS_PROVISIONAL);
    let pd_bus = I2c::new(
        p.I2C2, p.PA7, p.PA6, p.DMA1_CH1, p.DMA1_CH2, Irqs, i2c_config,
    );

    let mut can_configurator = CanConfigurator::new(p.FDCAN1, p.PA11, p.PA12, Irqs);
    can_configurator.set_bitrate(CAN_NOMINAL_BITRATE);
    can_configurator.set_fd_data_bitrate(CAN_DATA_BITRATE, false);
    let can_config = can_configurator.config().set_global_filter(
        GlobalFilter::reject_all().set_handle_extended_frames(NonMatchingFilter::IntoRxFifo0),
    );
    can_configurator.set_config(can_config);
    let can = can_configurator.into_normal_mode();

    let mut config_store = ConfigStore::new(Stm32ConfigFlash::new(p.FLASH));
    let settings = config_store
        .load()
        .ok()
        .flatten()
        .map_or(PersistentSettings::FACTORY_DEFAULT, |record| {
            record.settings
        });

    let watchdog = IndependentWatchdog::new(p.IWDG, IWDG_TIMEOUT_US_PROVISIONAL);

    spawner.spawn(tasks::status::status_task(status_output).unwrap());
    spawner.spawn(tasks::fan::fan_task(fan_pwm, fan_tach).unwrap());
    spawner.spawn(tasks::config::config_task(config_store).unwrap());
    let uid = NodeUid::from_bytes(embassy_stm32::uid::uid());
    spawner.spawn(tasks::pd_bus::pd_bus_task(pd_bus, mux_reset).unwrap());
    spawner.spawn(tasks::controller::controller_task(settings, uid, reset_flags).unwrap());
    spawner.spawn(tasks::can::can_task(can, can_standby).unwrap());
    spawner.spawn(tasks::supervisor::supervisor_task(watchdog).unwrap());

    loop {
        Timer::after_secs(60).await;
    }
}

fn capture_reset_flags() -> ResetFlags {
    let register = stm32_metapac::RCC.csr2().read();
    let mut flags = 0;
    if register.oblrstf() {
        flags |= ResetFlags::OPTION_BYTE;
    }
    if register.pinrstf() {
        flags |= ResetFlags::PIN;
    }
    if register.pwrrstf() {
        flags |= ResetFlags::POWER;
    }
    if register.sftrstf() {
        flags |= ResetFlags::SOFTWARE;
    }
    if register.iwdgrstf() {
        flags |= ResetFlags::INDEPENDENT_WATCHDOG;
    }
    if register.wwdgrstf() {
        flags |= ResetFlags::WINDOW_WATCHDOG;
    }
    if register.lpwrrstf() {
        flags |= ResetFlags::LOW_POWER;
    }
    stm32_metapac::RCC
        .csr2()
        .modify(|register| register.set_rmvf(true));
    ResetFlags::from_bits(flags)
}
